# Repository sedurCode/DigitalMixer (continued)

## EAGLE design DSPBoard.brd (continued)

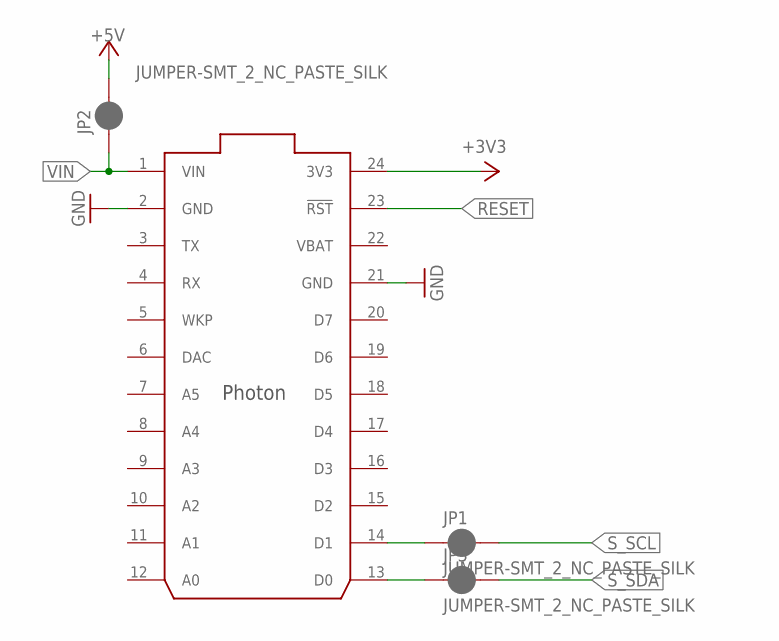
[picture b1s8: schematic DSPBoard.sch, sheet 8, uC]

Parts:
JP1, JP2, JP3: JUMPER-SMT_2_NC_PASTE_SILK; SMT-JUMPER_2_NC_PASTE_SILK
U$5: PHOTON_WITH_HEADERS; PHOTON

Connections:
+3V3: U$5.24 (3V3); also elsewhere on the board
+5V: JP2.2; also elsewhere on the board
GND: U$5.2 (GND), U$5.21 (GND); also elsewhere on the board
unnamed: JP1.1, U$5.14 (D1)
unnamed: JP3.1, U$5.13 (D0)
RESET: U$5.23 (!RST); also elsewhere on the board
S_SCL: JP1.2; also elsewhere on the board
S_SDA: JP3.2; also elsewhere on the board
VBAT: U$5.22 (VBAT)
VIN: JP2.1, U$5.1 (VIN)

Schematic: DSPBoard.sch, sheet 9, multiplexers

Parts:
C44, C152, C153, C154, C155: 100n; C0603
C124, C125, C126, C127: 10nF; C0603
IC13: 4520D; SO16
LED1, LED2, LED3, LED4, LED5, LED6, LED7, LED8: LEDCHIPLED_0805; CHIPLED_0805
MUX1, MUX2: 4051D; SO16
R10, R21, R22, R25, R28, R58, R84, R136, R137, R138, R140, R141: 10k; R0603
R26, R29, R30, R32, R42, R43, R44, R45: 470; R0603
U2, U3: PEC11R-4315F-N0012; PEC12R-4XXXF-SXXXX_1

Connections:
+3V3: C153.2, C154.2, C155.2, MUX1.7 (VEE), MUX1.16 (VCC), MUX2.16 (VCC), R25.1, R28.1, R58.1, R136.1, R137.1, R138.1, R140.1, R141.1; also elsewhere on the board
+5V: C44.1, C152.1, IC13.16 (VDD), MUX2.7 (VEE); also elsewhere on the board
AUXADC0: MUX1.3 (X); also elsewhere on the board
CV0: MUX1.13 (X0); also elsewhere on the board
CV1: MUX1.14 (X1); also elsewhere on the board
CV2: MUX1.15 (X2); also elsewhere on the board
CV3: MUX1.12 (X3); also elsewhere on the board
CV4: MUX1.1 (X4); also elsewhere on the board
CV5: MUX1.5 (X5); also elsewhere on the board
CV6: MUX1.2 (X6); also elsewhere on the board
CV7: MUX1.4 (X7); also elsewhere on the board
ENCODER0_0: C125.1, R10.2; also elsewhere on the board
ENCODER0_1: C124.1, R21.1; also elsewhere on the board
ENCODER1_0: C126.1, R22.2; also elsewhere on the board
ENCODER1_1: C127.1, R84.1; also elsewhere on the board
GND: C44.2, C124.2, C125.2, C126.2, C127.2, C152.2, C153.1, C154.1, C155.1, IC13.8 (VSS), MUX1.8 (GND), MUX2.8 (GND), R26.1, R29.1, R30.1, R32.1, R42.1, R43.1, R44.1, R45.1, U2.2 (B), U2.5 (NO), U3.2 (B), U3.5 (NO); also elsewhere on the board
LED_DRIVE: MUX2.3 (X); also elsewhere on the board
MUX1_A: IC13.3 (Q0), MUX1.11 (A)
MUX1_B: IC13.4 (Q1), MUX1.10 (B)
MUX1_C: IC13.5 (Q2), MUX1.9 (C)
MUX1_ENABLE: MUX1.6 (INH), R58.2
MUX1_ENABLE1: MUX2.6 (INH), R25.2
MUX2_A_A: IC13.11 (Q0), MUX2.11 (A)
MUX2_A_B: IC13.12 (Q1), MUX2.10 (B)
MUX2_A_C: IC13.13 (Q2), MUX2.9 (C)
MUX_CLK: IC13.1 (CLK), IC13.9 (CLK); also elsewhere on the board
unnamed: LED1.A, MUX2.13 (X0)
unnamed: LED2.A, MUX2.14 (X1)
unnamed: LED3.A, MUX2.15 (X2)
unnamed: LED4.A, MUX2.12 (X3)
unnamed: LED5.A, MUX2.1 (X4)
unnamed: LED6.A, MUX2.5 (X5)
unnamed: LED7.A, MUX2.2 (X6)
unnamed: LED8.A, MUX2.4 (X7)
unnamed: LED1.C, R45.2
unnamed: LED2.C, R44.2
unnamed: LED3.C, R43.2
unnamed: LED4.C, R42.2
unnamed: R10.1, R28.2, U2.1 (A)
unnamed: LED5.C, R32.2
unnamed: LED6.C, R30.2
unnamed: LED7.C, R29.2
unnamed: LED8.C, R26.2
unnamed: R22.1, R137.2, U3.1 (A)
unnamed: R84.2, R138.2, U3.3 (C)
unnamed: R21.2, R136.2, U2.3 (C)
SEL1: IC13.2 (EN), IC13.10 (EN); also elsewhere on the board
SEL2: IC13.7 (RES), IC13.15 (RES); also elsewhere on the board
SW0: R140.2, U2.4 (COM); also elsewhere on the board
SW1: R141.2, U3.4 (COM)

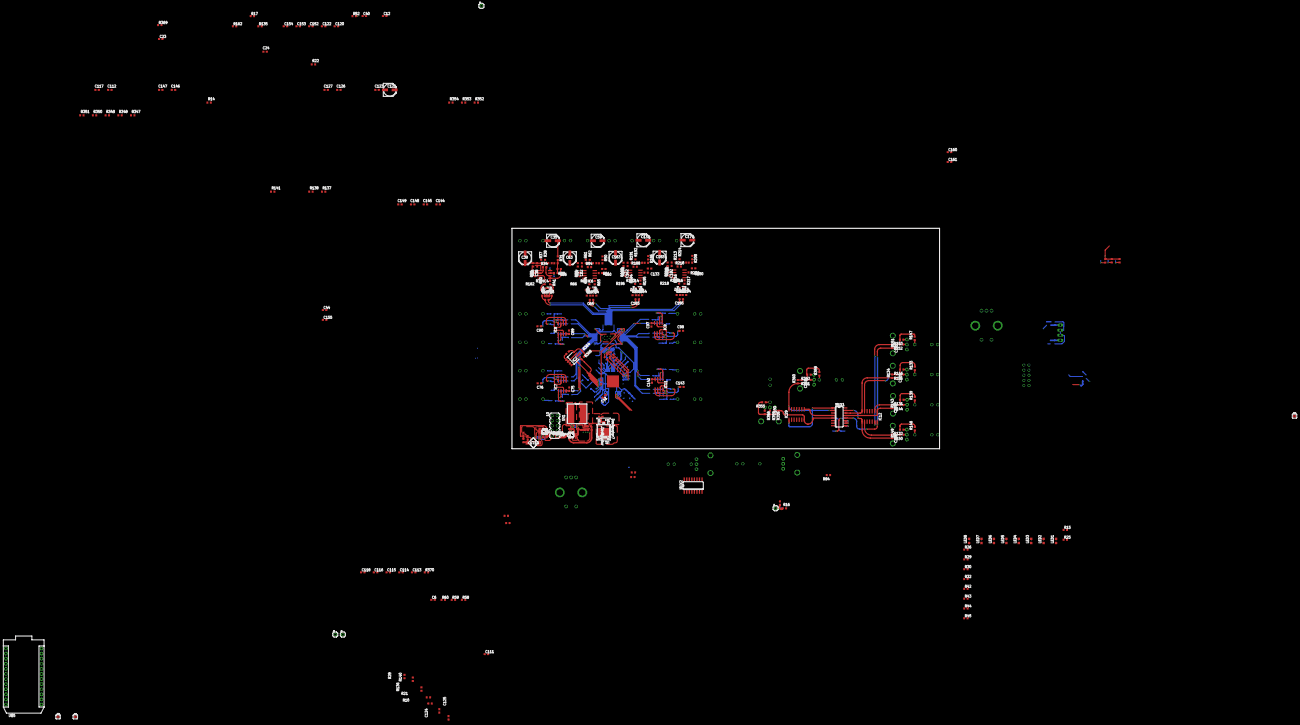
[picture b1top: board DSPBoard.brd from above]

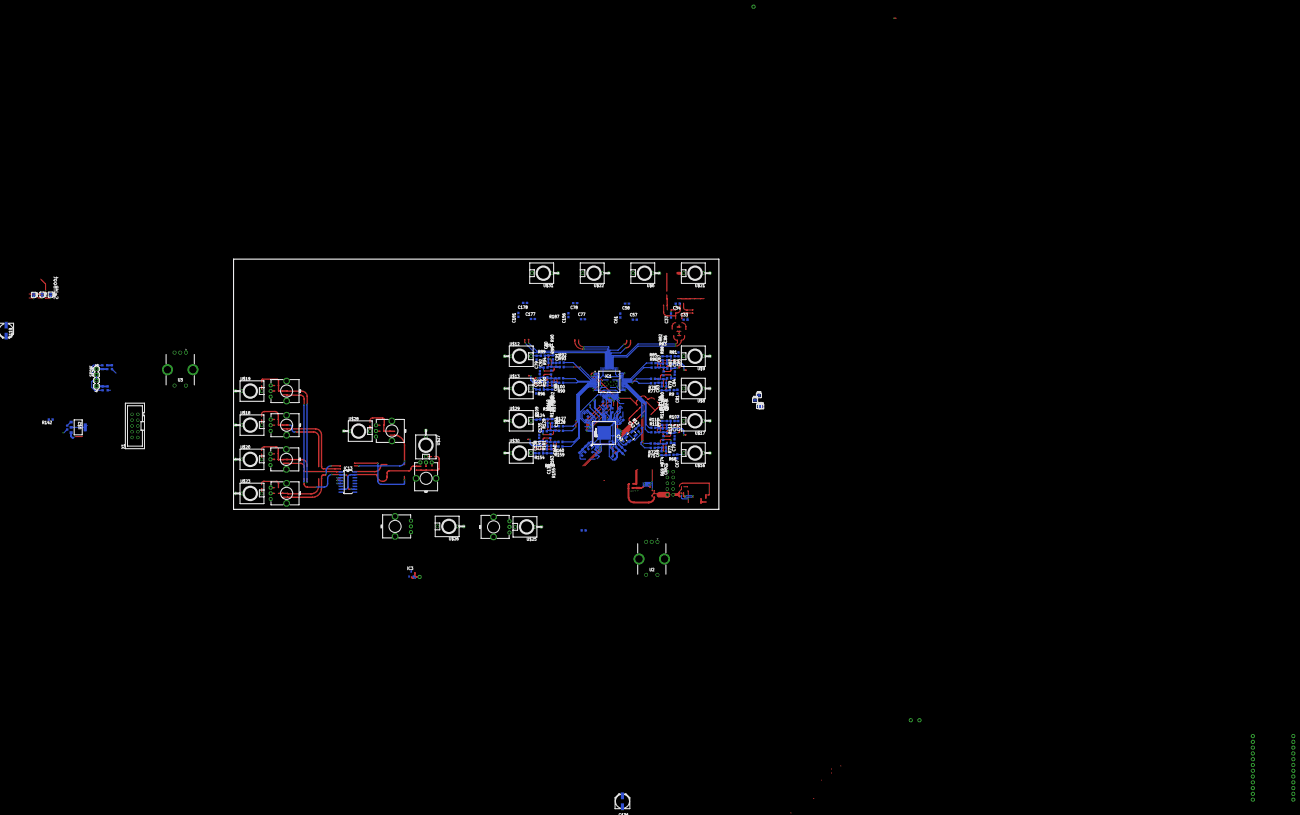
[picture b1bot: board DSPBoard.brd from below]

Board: 2 copper layers, 213.4 x 110.0 mm, 436 parts (181 on the bottom side), 253 nets.

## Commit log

2018-11-17 init2
2018-11-17 Backlink to CADLAB.io has been added.
2018-11-17 added changes to the control and clock sections
    Audio sections to do next
2018-11-17 im going to have to make it 2 projects to fit the pcb size limits
2018-11-18 start migration of parts to second board
2018-11-18 futher effort and set 3v3 analog
2018-11-19 added input single to differential circuit
2018-11-19 added analog output circuitry
2018-11-19 finished addign audio parts (still need to set values and check everyhting
2018-11-19 encoders and CV parts placed in sch
2018-11-19 ready to do the board
2018-11-20 tidying up on daves recommendations
2018-11-20 more tidying
2018-11-20 tidied analog outputs and tactile controls
2018-11-20 just need to add cycling diodes to schematic and board
2018-11-21 Ready to lay out
2018-11-21 rethinking the strategy
2018-11-21 schematic has multiplexed LEDs. Need to swap 0805 for 0604s
2018-11-28 removed LEDS
2018-11-29 Made progress in re-evaluating the design
2018-11-29 started laying out the psu
2018-11-30 some layout changes, need to make daves recomended changes
2018-12-02 double-check and confirm opamp audio gains (not CV)
2018-12-03 Chekcing and some bug fixes complete, plus psu layout touchup
2018-12-04 routing for the DSP
2018-12-06 grinding through
2018-12-07 rerouteclockreccomendataions
2018-12-08 relayingThechips
2018-12-13 board update
2018-12-13 continuing to layout
2018-12-16 MAybe I need to rethink this
2018-12-24 starting to consider making it a 2 board project
